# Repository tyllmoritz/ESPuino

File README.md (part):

# ESPuino - rfid-based musiccontroller based on ESP32 with I2S-DAC-support

## NEWS
* As the creator of TonUINO claims it's trademark right, my project has been renamed to ESPuino. I'm totally respecting this and have to admit that I've been not aware of that. However, I instantly renamed everything and hopefully I didn't forget any parts. Since my repository has moved, please make sure (at least if you're using git) to change the URL of your local repository. An explanation was kindly [written by user](https://github.com/biologist79/ESPuino/issues/81).
* Please note: inline with the renaming of the project, MQTT-topics were changed as well as they've been including the old name. Please make sure to change your local MQTT-configuration as well. Sorry to [those](https://github.com/biologist79/ESPuino/issues/83) that spent time on this to point out.
* EN: I've set up a primarily German-speaking community with much documentation. Also an international corner for non-German-speakers is available at https://forum.espuino.de. Github-Login can be used there but it's not necessary.
* DE: Ich habe ein primär deutschsprachiges Forum aufgesetzt, welches ich mit reichlich Doku versehen habe. Würde mich freuen, euch dort zu sehen: https://forum.espuino.de. Ihr könnt euch dort mit eurem Github-Login einloggen, jedoch auch "normal" anmelden. Dokumenation findet ihr insbesondere hier: https://forum.espuino.de/c/dokumentation/anleitungen/10
## Changelog
Moved to [another location](changelog.md) as it became to prominent here. Only last three events are kept:
* 25.02.2020: Added support for dynamic button-layout. Rotary-encoder is now optional and up to five buttons can be used.
* 25.02.2020: Actions can be freely assigned to buttons (multi-button(s), single-button(s) (short), single-button(s) (long))
* 25.02.2020: Added support for webcontrol: basic control (volume, play/pause, next, previous, first, last track) can now be controlled via webgui.
* 25.02.2020: Added support for .m4a and .wav-files.
* 26.02.2020: Shutdown via webgui is now available.
Thanks @QDaniel for the idea + basic implementation (first three features named above)!
## Known bugs
* Some webstreams don't run. Guess it's a combination of saturated connection-pool and lack of heap-memory. Works probably better if ESP32-WROVER (e.g. Lolin D32 pro) is used, as this chip has PSRAM. Advice: Don't enable modules (e.g. MQTT) if you don't need them as this could save memory (and trouble).
* English translation for webgui is currently pretty outdated. This will be fixed soon when i18n-support will be integrated.
## ESPuino - what's that?
The basic idea of ESPuino is to provide a way, to use the Arduino-platform for a music-control-concept that supports locally stored music-files without DRM-restrictions. This basically means that RFID-tags are used to direct a music-player. Even for kids this concept is simple: place an RFID-object (card, character) on top of a box and the music starts to play. Place another RFID-object on it and anything else is played. Simple as that.

The core of my implementation is based on the popular [ESP32 by Espressif](https://www.espressif.com/en/products/hardware/esp32/overview). Having WiFi-support out-of-the-box makes it possible to provide further features like an integrated FTP-server (to feed the player with music), smarthome-integration via MQTT, webradio and administration via webgui. However, my primary focus was to port the project to a modular base. Said this mp3-decoding is done in software with a dedicated uSD-card-slot and music-output is done via I2S-protocol. I did all my tests on [Adafruit's MAX98357A](https://learn.adafruit.com/adafruit-max98357-i2s-class-d-mono-amp/pinouts), [UDA1334](https://www.adafruit.com/product/3678) and [headphone-pcb](https://github.com/biologist79/ESPuino/tree/master/PCBs/Headphone%20with%20PCM5102a%20and%20TDA1308). Hopefully, not only in theory, other DACs that support I2S can be used as well.

## Hardware-setup
The heart of my project is an ESP32 on a [Wemos Lolin32 development-board](https://www.ebay.de/itm/4MB-Flash-WEMOS-Lolin32-V1-0-0-WIFI-Bluetooth-Card-Based-ESP-32-ESP-WROOM-32/162716855489). If ordered in China (Aliexpress, eBay e.g.) it's pretty cheap (around 4€) but even in Europe it's only around 8€. Make sure to install the drivers for the USB/Serial-chip (CP2102 e.g.). But probably it's better to use it's successor (which has battery-measurement already included): [Wemos Lolin D32](https://de.aliexpress.com/item/32808551116.html). Or, if you're planning to hear webstreams regularly, [Wemos Lolin D32 pro](https://de.aliexpress.com/item/32883116057.html) might be a good decision. It comes with uSD-slot onboard and because of its ESP32-WROVER-B has PSRAM included. PSRAM is used as webstream-cache and might be used more intensively in future.
* [MAX98357A (like Adafruit's)](https://de.aliexpress.com/item/32999952454.html)
* [uSD-card-reader; 3.3V only; supports SPI + SD-MMC](https://www.ebay.de/itm/Micro-SPI-Kartenleser-Card-Reader-2GB-SD-8GB-SDHC-Card-3-3V-ESP8266-Arduino-NEU/333796577968) or [cheaper](https://de.aliexpress.com/item/4000899753727.html)
* [RFID-reader RC-522](https://www.amazon.de/AZDelivery-Reader-Arduino-Raspberry-gratis/dp/B074S8MRQ7)
* [RFID-reader PN5180](https://de.aliexpress.com/item/4001278551831.html)
* [RFID-tags](https://www.amazon.de/AZDelivery-Keycard-56MHz-Schlüsselkarte-Karte/dp/B07TVJPTM7)
* [Neopixel-ring](https://de.aliexpress.com/item/32673883645.html)
* [Rotary Encoder](https://de.aliexpress.com/item/33041814942.html)
* [Buttons](https://de.aliexpress.com/item/32896285438.html)
* [Speaker](https://www.visaton.de/de/produkte/chassiszubehoer/breitband-systeme/fr-7-4-ohm)
* uSD-card: doesn't have to be a super-fast one; µC is limiting the throughput. Tested 32GB without any problems.
* uSD in SD-MMC (1 Bit) mode: Several devkits with onboard SD slot have support for this mode, e.g.: (https://de.aliexpress.com/item/4001229463219.html)
* optional replace the RFID-reader with a the better one: PN5180 comes with better RFID-range, less power-consumption and support for ISO-15693 / iCode SLIX2 tags (https://www.bing.com/shop?q=pn5180&FORM=SHOPTB)

## Getting Started
* Arduino-IDE can be used but you need to satisfy dependencies for all the libraries listed in `platformio.ini` manually.
* Instead I recommend to install Microsoft's [Visual Studio Code](https://code.visualstudio.com/). This is a popular and powerful IDE that gives you the ability to install tons of (well-supported) plugins.
* Install [Platformio Plugin](https://platformio.org/install/ide?install=vscode) into [Visual Studio Code](https://code.visualstudio.com/) and make sure to have a look at the [documentation](https://docs.platformio.org/en/latest/integration/ide/pioide.html). Step-by-step-manual is available [here](https://randomnerdtutorials.com/vs-code-platformio-ide-esp32-esp8266-arduino/.)
* Install [Git](https://git-scm.com/downloads) and make a copy ("clone") my repository to your local computer using `git clone https://github.com/biologist79/ESPuino.git`. Using git you can keep your local repository easily up to date without doing copy'n'paste. To keep it up to date run `git pull origin master`. Further infos [here}(https://stackoverflow.com/questions/1443210/updating-a-local-repository-with-changes-from-a-github-repository).
* (Optional) Install [Gitlens](https://marketplace.visualstudio.com/items?itemName=eamodio.gitlens) as plugin (to have advanced Git-support).
* Now, that the git-repository is saved locally, import this folder into Platformio as a project.
* There's a file called `platformio.ini`, that contains the configuration for different develboards (e.g. env:lolin32). Platformio supports hundrets of boards out of the box. So probably you need to change/extend that configuration. Guess Lolin32 is described in platformio.ini but you need Lolin D32, then lookup Platformio's [documentation](https://docs.platformio.org/en/latest/boards/espressif32/lolin_d32.html) to know what to change.
* `upload_port` and `monitor_port` should be autodetected (by the USB-ID of the serial-adapter). If this fails, please set these values depending on your operating system (Windows, Mac OS, Linux).
* Edit `src/settings.h` according your needs. Especially don't forget to set `HAL` depending on your develboard.
* Edit board-specific (`HAL`) config-file (e.g. `settings-lolin32.h` for Lolin32 or `settings-lolin_d32.h` for Lolin D32). If you're running a board that is not listed there: start with `settings-custom.h` and change it according your needs.
* Connect your develboard via USB, click the alien-head to the left and run `Upload and Monitor`. All libraries necessary should be fetched in background now followed by code-compilation. After that, your ESP32 is flashed with the firmware. Depending on your develboard it might me necessary to push a button in order to allow ESP32 to enter flashmode (not necessary für Lolin32, D32 und D32 pro).
* Now have a look at the serial-output at the bottom of Visual Studio Code's windows. At the first run there might appear a few error-messages (related to missing entries in NVS). Don't worry, this is just normal. However, make sure SD is running as this is mandatory!
* If everything ran fine, at the first run, ESPuino should open an access-point with the name "ESPuino". Join this WiFi with your computer (or mobile) and enter `192.168.4.1` to your webbrowser. Enter WiFi-credentials and the hostname. After saving the configuraton, restart ESPuino. Hint: I tried to connect this access-point via Android mobile. Basically that's no problem, but as my mobile detected there'd be no internet-connection, it keept LTE-connection open and prevented me from connecting to `192.168.4.1`. So if in doubts use a computer.
* After reboot ESPuino tries to join your WiFi (with the credentials previously entered). If that was successful, an IP is shown in the serial-console of Visual Studio Code. You can call ESPuino's GUI using a webbrowser via this IP; make sure to allow Javascript. If mDNS-feature is active in `src/settings.h`, you can use the hostname configured extended by .local instead the IP. So if you configured `espuino` as hostname, you can use `espuino.local` for webgui and FTP.
* Via FTP you can upload data (but don't expect it to be super fast). It's round about 185 kb/s if SD is in SPI-mode and 310 kB/s if SD is in MMC-mode.
* FTP needs to be activated after boot! Don't forget to assign action `ENABLE_FTP_SERVER` in `settings.h` to be able to activate it. Neopixel flashes green (1x) if enabling was successful. It'll be disabled automatically after next reboot. Means: you have to enable it every time you need it (if reboot was in between). Sounds annoying and maybe it is, but's running this way in order to have more heap-memory available (for webstream) if FTP isn't running.
* Via webbrowser you can configure various settings and pair RFID-tags with actions. If MQTT/FTP-support was not compiled, their config-tabs won't appear.

## Prerequisites / tipps
* Open settings.h
* choose if optional modules (e.g. MQTT, FTP, Neopixel) should be compiled/enabled
* Make sure to edit/review button-layout. Default-design is three buttons and a rotary-encoder. All actions available are listed in `values.h` (values >= 100).
* For debugging-purposes serialDebug can be set to ERROR, NOTICE, INFO or DEBUG.
* If MQTT=yes, set the IP or hostname of the MQTT-server accordingly and check the MQTT-topics (states and commands)
* Advice: don't enable MQTT if there's no broker around because network-timeouts can really be a PITA.
* If Neopixel enabled: set NUM_LEDS to the LED-number of your Neopixel-ring and define the Neopixel-type using `#define CHIPSET`
* If you're using Arduino-IDE please make sure to change ESP32's partition-layout to `No OTA (2MB APP/2MB Spiffs)` as otherwise the sketch won't fit into the flash-memory.
* Open board-specific config-file and edit according your needs.
* If you want to monitor battery's voltage, make sure to enable `MEASURE_BATTERY_VOLTAGE`. Use a voltage-divider as voltage of a LiPo is way too high for ESP32 (only 3.3V supported!). For my tests I connected VBat with a serial connection of 130k + 130k resistors (VBat(+)--130k--X--130k--VBat(-)). X is the measure-point where to connect the GPIO to. If using Lolin D32 or Lolin D32 pro, make sure to leave both resistor-values unchanged at 100k. Same for GPIO: unchanged at 35.
Please note: via GUI upper and lower voltage cut-offs for visualisation of battery-voltage (Neopixel) is available. Additional GUI-configurable values are interval (in minutes) for checking battery voltage and the cut off-voltage below whose a warning is shown via Neopixel.
* If you're using a headphone-pcb with a [headphone jack](https://www.conrad.de/de/p/cliff-fcr1295-klinken-steckverbinder-3-5-mm-buchse-einbau-horizontal-polzahl-3-stereo-schwarz-1-st-705830.html) that has a pin to indicate if there's a plug, you can use this signal along with the feature `HEADPHONE_ADJUST_ENABLE` to limit the maximum headphone-voltage automatically. As per default you have to invert this signal (with a P-channel MOSFET) and connect it to GPIO22.
* Enabling `SHUTDOWN_IF_SD_BOOT_FAILS` is really recommended if you run your ESPuino in battery-mode without having a restart-button exposed to the outside of ESPuino's enclosure. Because otherwise there's no way to restart your ESPuino and the error-state will remain until battery is empty (or you open the enclosure, hehe).
* Enabling `PLAY_LAST_RFID_AFTER_REBOOT` will tell ESPuino to remember the last RFID-tag played after next reboot. So rebooting ESPuino will end up in autoplay. I don't really recommend this feature because if you use it along with a webstream, in case of streaming-issues this might end up in an infinite loop.

## SD-card: SPI or SD-MMC (1 bit)-mode?
Having SD working is mandatory. However, there are two modes available to access SD-cards: SPI and SD-MMC (1 bit).<br />
Advantages SD-MMC (1 bit) over SPI:
* Needs only three GPIOs (instead of four)
* It's faster. FTP-upload: 298 kiB vs 178 kiB. HTTP-upload: 372 kiB vs 184 kiB. (tested with filesize of 70.7 MiB.<br />
So why using SPI if SD-MMC seems to be better? The primary problem of SD-MMC is: you cannot choose different GPIOs. That doesn't sound bad but this can (depending on the uSD-card-reader-module) be a problem because maybe GPIO2 is pulled HIGH to 3.3V by a 10k-resistor. For example this is the case when using the reader-module named above in hardware-setup. It's a problem because if GPIO2 is pulled high at boot, ESP32 doesn't enter flash-mode. As soon as flash-mode is entered, it's no longer a problem. However, this behaviour can be an issue if ESP32 is deeply "burried" in ESPuino's enclosure and you want to update its firmware. But fortunately there's a way to bypass this problem: remove the [pullup-resistor shown in the picture](https://raw.githubusercontent.com/biologist79/ESPuino/master/pictures/Pullup-removal.jpg). It can be removed safely because if MMC-mode is set, pullup is done in software using `pinMode(2, INPUT_PULLUP);`. So it's not really a problem but you have to take note of that!

## RFID: RC522 or PN5180?
RC522 is so to say the Tonuino-standard. It's cheap and works, but RFID-tag has to be placed near the reader. PN5180 instead has better RFID range/sensitivity and can read ISO-15693 / iCode SLIX2-tags aka 'Tonies' (you need a password to read Tonies). You can also wake-up the board with the card. Disadvantages: is a bit more expensive and needs more GPIOs (6/7 instead of 4). Refer PN5180's wire-section below for further informations. Hint: if using 3.3V make sure to connect PN5180 to +5V AND 3.3V. Sounds weird but it's necessary.

## 3.3 or 5V?
* Why 3.3V? Because: if you plan to use battery-mode with a LiPo, there's no 5 V available (unless USB is connected).
That's why my design's focus is 3.3 V. If you want to use 5 V - do so, but be advised it's not compatible with LiPo-battery-mode. The Mosfet-circuit for saving power in deepsleep (see [Lolin32-schematics](https://github.com/biologist79/ESPuino/blob/master/PCBs/Wemos%20Lolin32/Pictures/Tonuino%20V2-Schematics.pdf) as reference) works as well for 5 V.
* MAX98357a: provides more power at 5 V but also runs at 3.3 V. Anyway: it's still loud enough (in my opinion).
* Neopixel: specification says it needs 5 V but also runs at 3.3 V.
* RC522: needs 3.3 V (don't power with 5 V!)
* PN5180: at 3.3 V make sure to connect both 5 V and 3.3 V-pins to 3.3 V.
* SD: needs 3.3 V but if voltage-regulator is onboard, it can be connected to 5 V as well
* Rotary encoder: 3.3 V (don't power with 5 V! Encoder doens't care if connected to 3.3 or 5 V, but GPIOs of ESP32 do!)

## Wiring (general)
Depending on the develboard you're using and the needs you have, there are different options available.
A lot of wiring is necessary to get ESPuino working. After my first experiments on a breadboard I soldered all the stuff onto a PCB in order to avoid wild-west-cabling. Especially for the interconnect between µC and uSD-card-reader make sure to use short wires (like 10cm or so)! As of my experience with a breadbord, male/male-connectors are better than female/female-connectors. Important: you can easily connect another I2S-DACs by just connecting them in parallel to the I2S-pins (DIN, BCLK, LRC). This is true for example if you plan to integrate a [line/headphone-pcb](https://www.adafruit.com/product/3678). In general, this runs fine. But unfortunately especially this board lacks of a headphone jack, that takes note if a plug is inserted or not. Best way is to use a [headphone jack](https://www.conrad.de/de/p/cliff-fcr1295-klinken-steckverbinder-3-5-mm-buchse-einbau-horizontal-polzahl-3-stereo-schwarz-1-st-705830.html) that has a pin that is pulled to GND, if there's no plug and vice versa. Using for example a MOSFET-circuit, this GND-signal can be inverted in a way, that MAX98357.SD is pulled down to GND if there's a plug. Doing that will mute MAX98537a and so turn off the speaker immediately if there's a plug and vice versa. Have a look at the PCB-folder in order to view the detailed solution. Here's an example for such a [headphone-pcb](https://github.com/biologist79/ESPuino/tree/master/PCBs/Headphone%20with%20PCM5102a%20and%20TDA1308) that makes use of GND.<br />
Have a look at the PCB-folder. I provided PCBs for a number of develboards. Probably this makes things easier for you.

## Wiring (2 SPI-instances: RC522 + SD + 3 buttons + rotary-encoder)
Uses two SPI-instances. The first one for the RFID-reader and the second for SD-card-reader. This is also the [setup, I personally use](https://github.com/biologist79/ESPuino/tree/master/PCBs/Wemos%20Lolin32).<br />
| ESP32 (GPIO)  | Hardware              | Pin    | Comment                                                      |
| ------------- | --------------------- | ------ | ------------------------------------------------------------ |
| 3.3 (5) V     | SD-reader             | VCC    | Connect to p-channel MOSFET for power-saving when µC is off  |
| GND           | SD-reader             | GND    |                                                              |
| 15            | SD-reader             | CS     |                                                              |
| 13            | SD-reader             | MOSI   |                                                              |
| 16            | SD-reader             | MISO   |                                                              |
| 14            | SD-reader             | SCK    |                                                              |
| 3.3 V         | RFID-reader           | 3.3V   | (Connect directly to GPIO 17 for power-saving when µC is off)  |
| GND           | RFID-reader           | GND    |                                                              |
| 21            | RFID-reader           | CS/SDA |                                                              |
| 23            | RFID-reader           | MOSI   |                                                              |
| 19            | RFID-reader           | MISO   |                                                              |
| 18            | RFID-reader           | SCK    |                                                              |
| 5 / 3.3 V     | MAX98357              | VIN    | Connect to p-channel MOSFET for power-saving when µC is off  |
| GND           | MAX98357              | GND    |                                                              |
| 25            | MAX98357              | DIN    |                                                              |
| 27            | MAX98357              | BCLK   |                                                              |
| 26            | MAX98357              | LRC    |                                                              |
| ---           | MAX98357              | SD     | Info: if pulled down to GND amp will turn off                |
| 34            | Rotary encoder        | CLK    | Change CLK with DT if you want to change the direction of RE |
| 35            | Rotary encoder        | DT     | Change CLK with DT if you want to change the direction of RE |
| 32            | Rotary encoder        | BUTTON |                                                              |
| 3.3 V         | Rotary encoder        | +      |                                                              |
| GND           | Rotary encoder        | GND    |                                                              |
| 4             | Button (next)         |        |                                                              |
| GND           | Button (next)         |        |                                                              |
| 2             | Button (previous)     |        |                                                              |
| GND           | Button (previous)     |        |                                                              |
| 5             | Button (pause/play)   |        |                                                              |
| GND           | Button (pause/play)   |        |                                                              |
| 3.3 V         | Neopixel              | V      | Connect to p-channel MOSFET for power-saving when µC is off  |
| GND           | Neopixel              | G      |                                                              |
| 12            | Neopixel              | DI     |                                                              |
| 17            | N-channel Mosfet      | Gate   |                                                              |
| 33            | Voltage-divider / BAT |        | Optional: voltage-divider to monitor battery-voltage         |
| 22            | Headphone jack        |        | Optional: if pulled to ground, headphone-volume is set       |

Optionally, GPIO 17 can be used to drive a Mosfet-circuit in order to switch off peripherals (SD, Neopixel, RFID and MAX98357a) if ESP32 is in deepsleep. Please refer the schematics for my [Lolin32-PCB](https://github.com/biologist79/ESPuino/blob/master/PCBs/Wemos%20Lolin32/Pictures/Tonuino-Lolin32-Schematics.pdf) for further informations. If you need further informations on transistor-circuits visit this [website](https://dl6gl.de/schalten-mit-transistoren.html). <br />
In general I recommend using a [uSD-card-reader](https://www.ebay.de/itm/Micro-SPI-Kartenleser-Card-Reader-2GB-SD-8GB-SDHC-Card-3-3V-ESP8266-Arduino-NEU/333796577968) that can be run solely with 3.3V (doesn't have a voltage-regulator). This is because if 3.3V go through the voltage regulator a small voltage-drop will be introduced, which may lead to SD-malfunction as the resulting voltage is a bit too low. Vice versa if you want to connect your reader solely to 5V, make sure to have one WITH a voltage regulator :-). And by the way: when LiPo-battery is connected, there's no 5V. That's why I designed my [Lolin-PCBs](https://github.com/biologist79/ESPuino/tree/master/PCBs/Wemos%20Lolin32) with 3.3V only.

## Wiring (SD-card in 1 Bit SD-MMC mode) different to above
| ESP32 (GPIO)  | Hardware              | Pin    | Comment                                                      |
| ------------- | --------------------- | ------ | ------------------------------------------------------------ |
| --            | SD-reader             | CS     | no CS required                                               |
| 15            | SD-reader             | MOSI   |                                                              |
| 2             | SD-reader             | MISO   | make sure there's no [hardware-pullup](https://raw.githubusercontent.com/biologist79/ESPuino/master/pictures/Pullup-removal.jpg) for MISO |
| 14            | SD-reader             | SCK    |                                                              |

Make sure to enable `SD_MMC_1BIT_MODE` if you want to use this feature. Don't(!) enable `SINGLE_SPI_ENABLE`. SD-MMC-mode requires these fixed PINs listed above. You can find a good comparison of different SD-card-modes here: (https://www.instructables.com/Select-SD-Interface-for-ESP32/).
Advice: Double check that above PINs are not used elsewhere (e.g. GPIO2 is used as PREVIOUS_BUTTON as per default in settings.h).

## Wiring (1 SPI-instance: RC522 + SD + 3 buttons + rotary-encoder) [EXPERIMENTAL, maybe not working!]
Basically the same as using 2 SPI-instances but...
In this case RFID-reader + SD-reader share SPI's SCK, MISO and MOSI. But make sure to use different CS-pins. Have to admit I had some problems to get this running. Seems to be connected properly, but nothing happens when an RFID-tag is applied. Maybe anybody else wants to point out :-)

| ESP32 (GPIO)  | Hardware              | Pin    | Comment                                                      |
| ------------- | --------------------- | ------ | ------------------------------------------------------------ |
| 3.3 (5) V     | SD-reader             | VCC    | Connect to p-channel MOSFET for power-saving when µC is off  |
| GND           | SD-reader             | GND    |                                                              |
| 15            | SD-reader             | CS     | Don't share with RFID!                                       |
| 3.3 V         | RFID-reader           | 3.3V   | Connect directly to GPIO 17 for power-saving when µC is off  |
| GND           | RFID-reader           | GND    |                                                              |
| 21            | RFID-reader           | CS/SDA | Don't share with SD!                                         |
| 23            | RFID+SD-reader        | MOSI   |                                                              |
| 19            | RFID+SD-reader        | MISO   |                                                              |
| 18            | RFID+SD-reader        | SCK    |                                                              |
| 5 / 3.3 V     | MAX98357              | VIN    | Connect to p-channel MOSFET for power-saving when µC is off  |
| GND           | MAX98357              | GND    |                                                              |
| 25            | MAX98357              | DIN    |                                                              |
| 27            | MAX98357              | BCLK   |                                                              |
| 26            | MAX98357              | LRC    |                                                              |
| ---           | MAX98357              | SD     | Info: if pulled down to GND amp will turn off                |
| 34            | Rotary encoder        | CLK    | Change CLK with DT if you want to change the direction of RE |
| 35            | Rotary encoder        | DT     | Change CLK with DT if you want to change the direction of RE |
| 32            | Rotary encoder        | BUTTON |                                                              |
| 3.3 V         | Rotary encoder        | +      |                                                              |
| GND           | Rotary encoder        | GND    |                                                              |
| 4             | Button (next)         |        |                                                              |
| GND           | Button (next)         |        |                                                              |
| 2             | Button (previous)     |        |                                                              |
| GND           | Button (previous)     |        |                                                              |
| 5             | Button (pause/play)   |        |                                                              |
| GND           | Button (pause/play)   |        |                                                              |
| 5 / 3.3 V     | Neopixel              | V      | Connect to p-channel MOSFET for power-saving when µC is off  |
| GND           | Neopixel              | G      |                                                              |
| 12            | Neopixel              | DI     |                                                              |
| 17            | N-channel Mosfet      | Gate   |                                                              |
| 33            | Voltage-divider / BAT |        | Optional: voltage-divider to monitor battery-voltage         |
| 22            | Headphone jack        |        | Optional: if pulled to ground, headphone-volume is set       |

## Wiring (PN5180 instead of MFRC522) different to above
PN5180-reader needs at least two more GPIOs: RESET and BUSY. Double check pin-conflicts! `RFID_READER_TYPE_PN5180` needs to be enabled to use this feature. Make sure to disable `RFID_READER_TYPE_MFRC522` if doing so!
You can enable low power card-detection with `PN5180_ENABLE_LPCD`, but this needs another GPIO for IRQ. With low power card detection (LPCD) you can wake-up the ESP32 from deep-sleep just by applying a card to the reader. You need a PN5180-firmware >= 4.0. Most china-boards comes with older firmware. The latest firmware can be flashed with this [project](https://github.com/abidxraihan/PN5180_Updater_ESP32).

| ESP32 (GPIO)  | Hardware              | Pin    | Comment                                                           |
| ------------- | --------------------- | ------ | ----------------------------------------------------------------- |
| 3.3 V         | PN5180 RFID-reader    | 3.3V   | Connect directly to GPIO 17 for power-saving when µC is off       |
| 3.3 V         |                       | 3.3V   | For low power card detection mode (LPCD) connect directly to 3.3V |
| 5 / 3.3 V     | PN5180 RFID-reader    | 5V     | Don't forget to connect this pin the same way as 3.3V             |
| GND           | PN5180 RFID-reader    | GND    |                                                                   |
| 21            | PN5180 RFID-reader    | CS/SDA | Same as MFRC522. Don't share with SD!                             |
| 23            | PN5180 RFID-reader    | MOSI   | Same as MFRC522                                                   |
| 19            | PN5180 RFID-reader    | MISO   | Same as MFRC522                                                   |
| 18            | PN5180 RFID-reader    | SCK    | Same as MFRC522                                                   |
| 16            | PN5180 RFID-reader    | BUSY   | be aware of SD MISO if running in SPI mode                        |
| 22            | PN5180 RFID-reader    | RST    | be aware of Headphone jack PIN                                    |
| 39            | PN5180 RFID-reader    | IRQ    | optional, used for low power card detection (LPCD)                |

## Wiring (custom) / different pinout
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
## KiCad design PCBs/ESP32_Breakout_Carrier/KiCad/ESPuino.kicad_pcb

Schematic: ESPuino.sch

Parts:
J1: SD-Card Reader; PinHeader_1x06_P2.54mm_Vertical
J2: RFID-RC522; PinHeader_1x08_P2.54mm_Vertical
J3: Adafruit MAX98357; PinHeader_1x07_P2.54mm_Vertical
J4: Rotary Encode; PinHeader_1x05_P2.54mm_Vertical
J5: Next; PinHeader_1x02_P2.54mm_Vertical
J6: Prev; PinHeader_1x02_P2.54mm_Vertical
J7: Pause; PinHeader_1x02_P2.54mm_Vertical
J8: WS2812; PinHeader_1x03_P2.54mm_Vertical
J9: Power; PinHeader_1x02_P2.54mm_Vertical
Q1: BC337; TO-92_Inline_Wide
Q2: IRF9540N; TO-220-3_Vertical
R1, R4: 10k; 0207_9
R5: 4,7k; 0207_9
U1: ESP32-DEVKITC-32U; MODULE_ESP32-DEVKITC-32U

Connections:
3.3V: J4.2, U1.1
BUTTON_NEXT_PIN: J6.2, U1.26
BUTTON_PLAY_PAUSE_PIN: J7.2, U1.29
BUTTON_PREVIOUS_PIN: J5.2, U1.8
GND: J1.1, J2.3, J3.2, J4.1, J5.1, J6.1, J7.1, J8.1, J9.1, Q1.3 (E), R4.2, U1.14, U1.32, U1.38
GPIO-17: J2.1, R5.2, U1.28
MAX98357_BLCK: J3.6, U1.11
MAX98357_DIN: J3.5, U1.9
MAX98357_LRC: J3.7, U1.10
NEOPIXEL_DI: J8.2, U1.13
unnamed: Q1.1 (C), Q2.1 (G), R1.2
unnamed: Q1.2 (B), R4.1, R5.1
RFID_MISO: J2.5, U1.31
RFID_MOSI: J2.6, U1.37
RFID_RST: J2.2, U1.36
RFID_SCK: J2.7, U1.30
RFID_SDA: J2.8, U1.33
ROTARY_BUTTON: J4.5, U1.7
ROTARY_CLR: J4.3, U1.5
ROTARY_DT: J4.4, U1.6
SD-CARD_CS: J1.6, U1.23
SD-CARD_MISO: J1.3, U1.27
SD-CARD_MOSI: J1.4, U1.15
SD-CARD_SCK: J1.5, U1.12
SWITCHED_VCC: J1.2, J3.1, J8.3, Q2.2 (D)
VCC: J9.2, Q2.3 (S), R1.1, U1.19

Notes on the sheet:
Breakout Boards
Inputs Interfaces
Switched 5V (Deep Sleep)
ESP-32
Power Supply

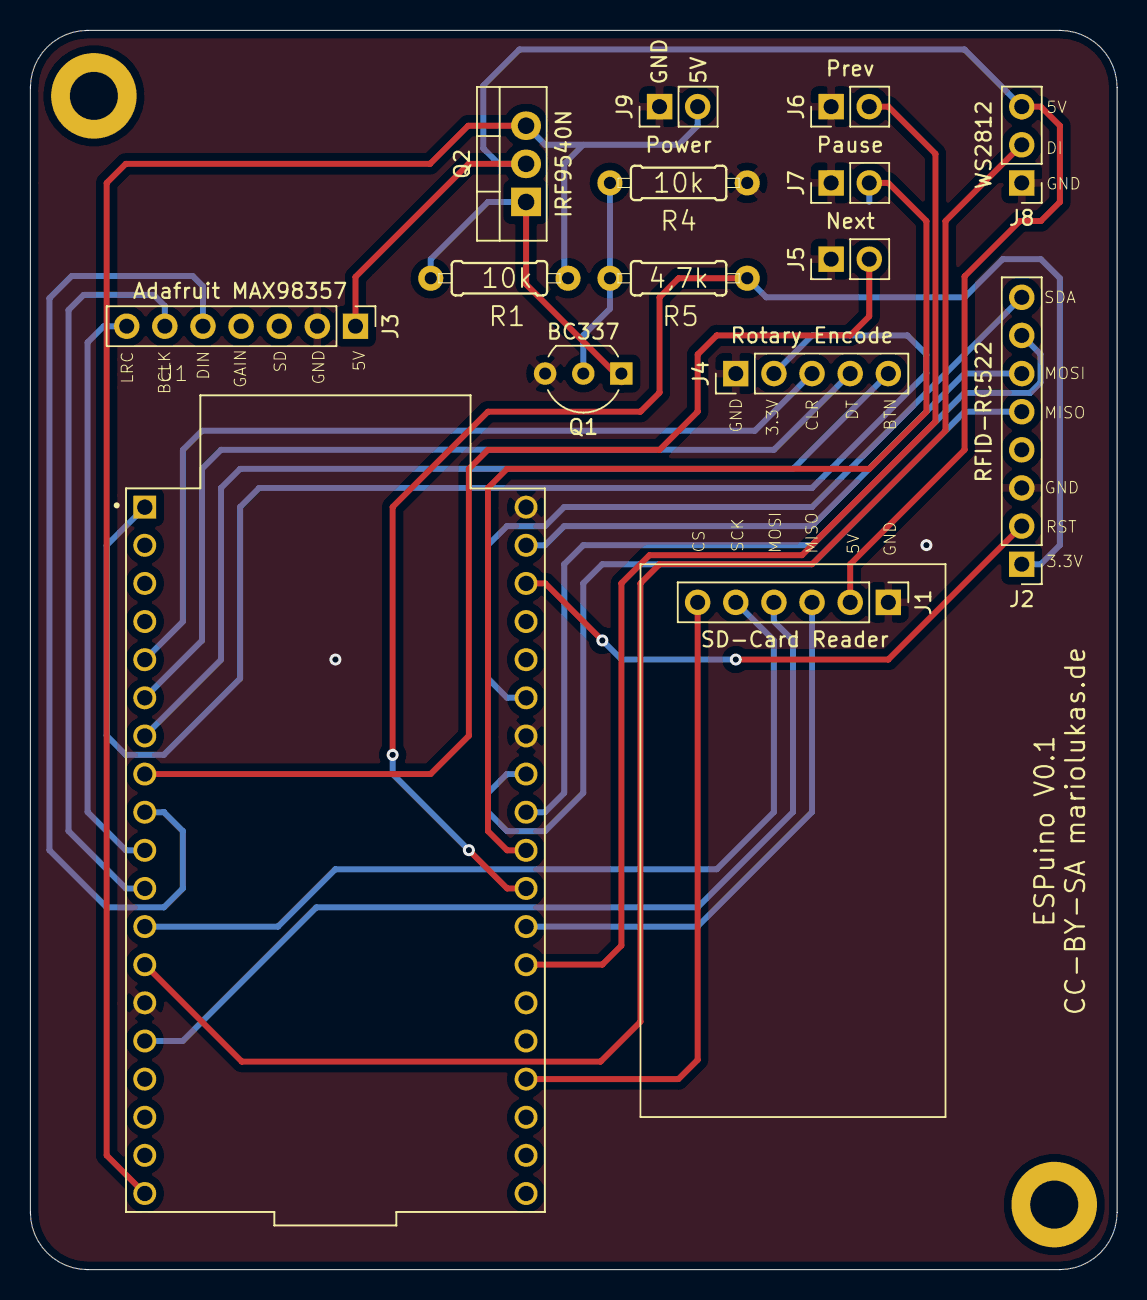
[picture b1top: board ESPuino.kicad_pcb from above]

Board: 2 copper layers, 72.4 x 82.6 mm, 15 parts (0 on the bottom side), 26 nets.

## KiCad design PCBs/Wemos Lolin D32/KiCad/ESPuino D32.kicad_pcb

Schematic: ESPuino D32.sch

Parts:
H1, H2, H3, H4: MountingHole; MountingHole_3.2mm_M3
J1: MAX98357a; PinSocket_1x07_P2.54mm_Vertical
J2: Neopixel; JST_PH_B3B-PH-K_1x03_P2.00mm_Vertical
J3: to_Headphone; IDC-Header_2x03_P2.54mm_Vertical
J4: RotEncoder; JST_PH_B5B-PH-K_1x05_P2.00mm_Vertical
J5: Next-Bt; JST_PH_B2B-PH-K_1x02_P2.00mm_Vertical
J6: RFID; JST_PH_B6B-PH-K_1x06_P2.00mm_Vertical
J7: Prev-Bt; JST_PH_B2B-PH-K_1x02_P2.00mm_Vertical
J8: PPlay-Bt; JST_PH_B2B-PH-K_1x02_P2.00mm_Vertical
J9: Reset; JST_PH_B2B-PH-K_1x02_P2.00mm_Vertical
J10: uSD-Reader; PinSocket_1x06_P2.54mm_Vertical
M1: LolinD32
Q1: NDP6020P; TO-220-3_Vertical
Q2: IRF530NPbF; TO-220-3_Vertical
R1, R3: 100k; R_Axial_DIN0204_L3.6mm_D1.6mm_P7.62mm_Horizontal
R2: 1k; R_Axial_DIN0204_L3.6mm_D1.6mm_P7.62mm_Horizontal
R4: 10k; R_Axial_DIN0204_L3.6mm_D1.6mm_P7.62mm_Horizontal

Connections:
+3V3: J4.2, M1.16 (3V), Q1.3, R3.2
BUT_NEXT: J5.1, M1.21 (4)
BUT_PPLAY: J8.1, M1.24 (5)
BUT_PREV: J7.1, M1.19 (2)
CS_RFID: J6.1, M1.27 (21)
CS_SD: J10.5, M1.18 (15)
DIN: J1.5, J3.1, M1.9 (25)
EN: J9.1, M1.3 (EN)
GND: J1.2, J2.1, J3.4, J4.1, J5.2, J6.5, J7.2, J8.2, J9.2, J10.1, M1.17 (GND), M1.32 (GND), Q2.3, R4.1
Headphone: J1.3, J3.6, M1.30 (22)
I2S_BCLK: J1.6, J3.3, M1.7 (27)
I2S_LRC: J1.7, J3.5, M1.8 (26)
MISO_RFID: J6.4, M1.26 (19)
MISO_SD: J10.2, M1.22 (16)
MOSI_RFID: J6.3, M1.31 (23)
MOSI_SD: J10.4, M1.4 (13)
NEO_DO: J2.2, M1.5 (12)
unnamed: J1.4, R1.1
unnamed: M1.23 (17), R2.2
unnamed: Q1.1, Q2.2, R3.1
unnamed: Q2.1, R2.1, R4.2
ROTENC_BUT: J4.3, M1.11 (32)
ROTENC_CLK: J4.4, M1.12 (34)
ROTENC_DT: J4.5, M1.10 (33)
SCK_RFID: J6.2, M1.25 (18)
SCK_SD: J10.3, M1.6 (14)
SW_Power3.3: J1.1, J2.3, J3.2, J6.6, J10.6, Q1.2, R1.2

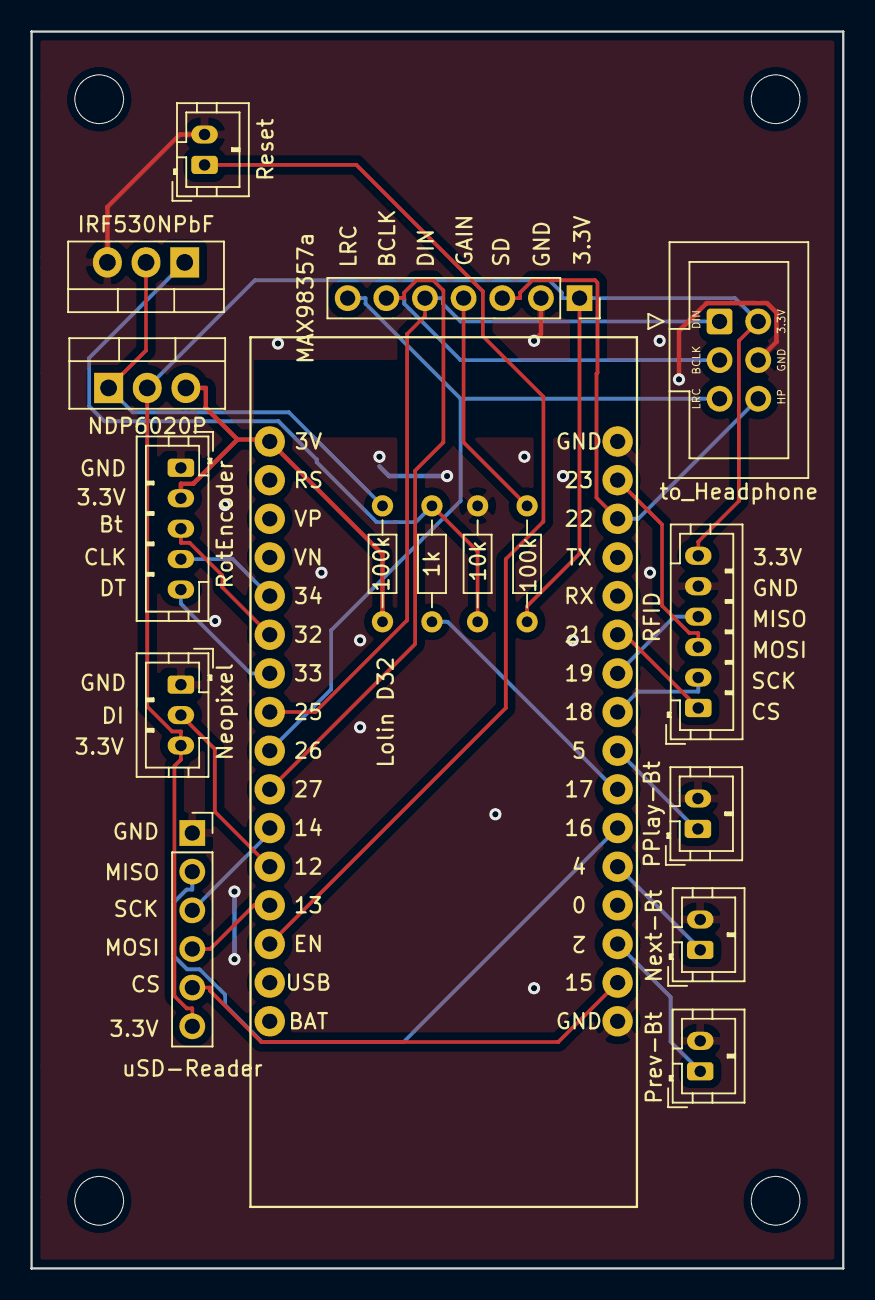
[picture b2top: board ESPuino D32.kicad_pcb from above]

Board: 2 copper layers, 53.3 x 81.3 mm, 21 parts (0 on the bottom side), 27 nets.

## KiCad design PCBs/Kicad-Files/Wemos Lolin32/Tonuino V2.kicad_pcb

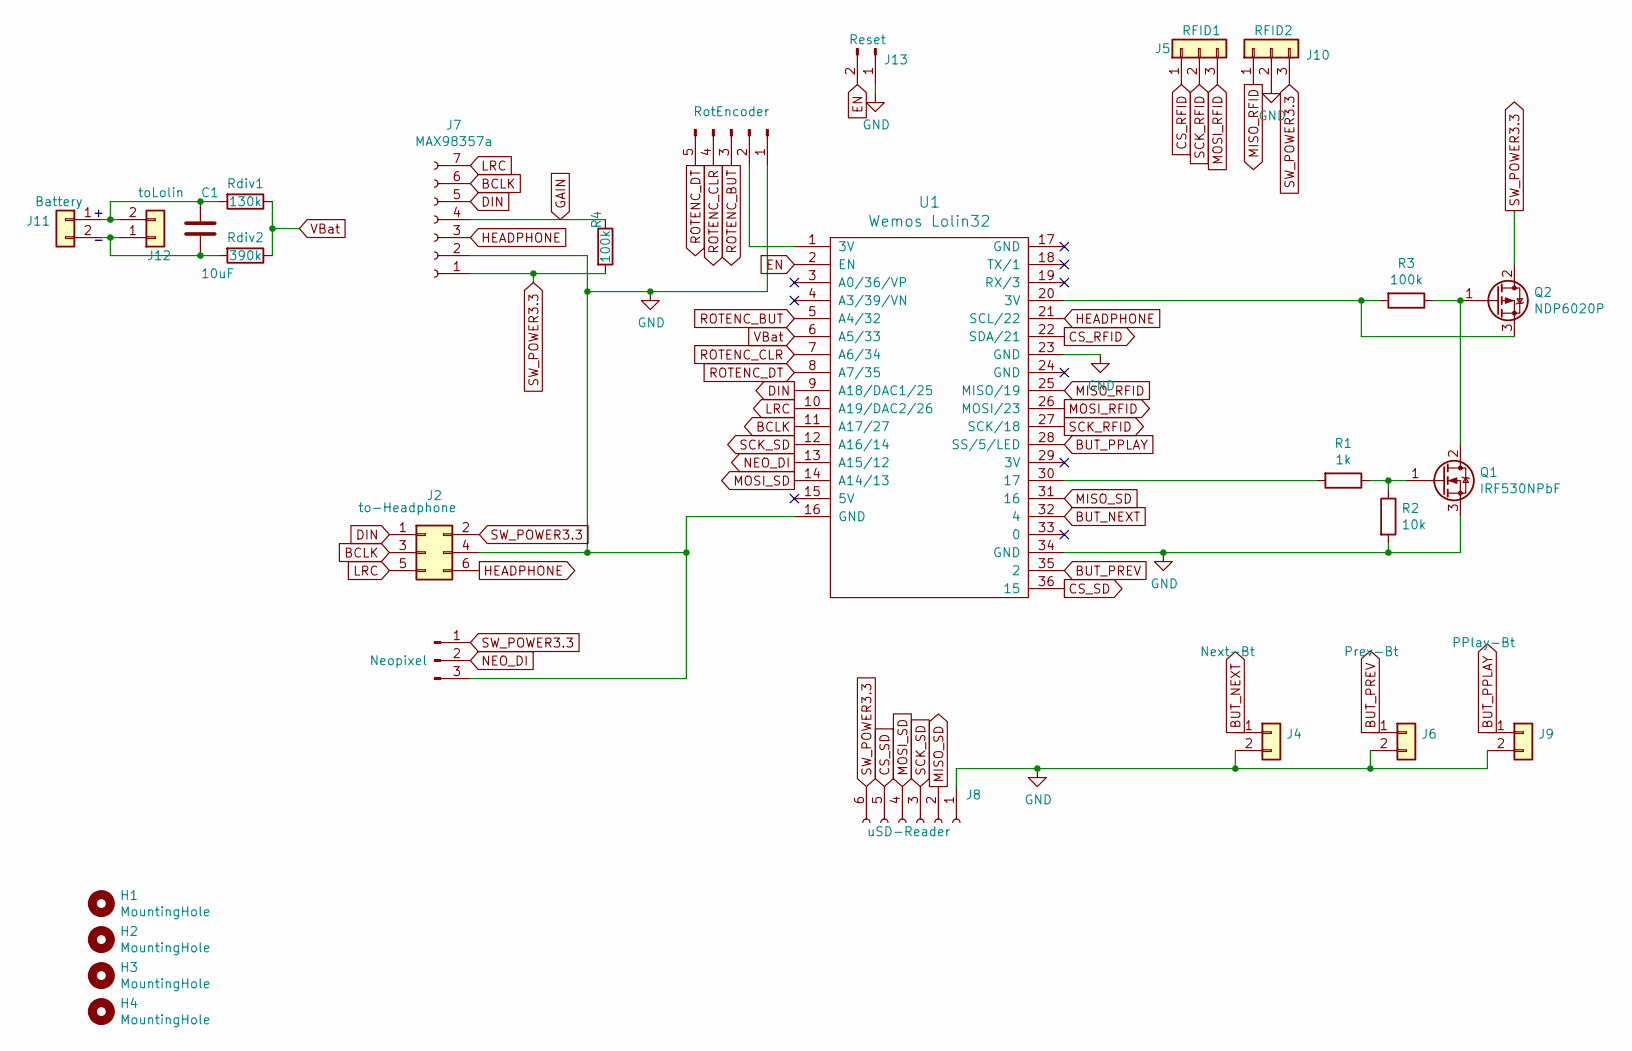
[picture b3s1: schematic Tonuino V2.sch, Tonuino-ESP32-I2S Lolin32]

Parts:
C1: 10uF; CP_Radial_D4.0mm_P2.00mm
H1, H2, H3, H4: MountingHole; MountingHole_3.2mm_M3
J1: Neopixel; JST_PH_B3B-PH-K_1x03_P2.00mm_Vertical
J2: to-Headphone; IDC-Header_2x03_P2.54mm_Vertical
J3: RotEncoder; JST_PH_B5B-PH-K_1x05_P2.00mm_Vertical
J4: Next-Bt; JST_PH_B2B-PH-K_1x02_P2.00mm_Vertical
J5: RFID1; JST_PH_B3B-PH-K_1x03_P2.00mm_Vertical
J6: Prev-Bt; JST_PH_B2B-PH-K_1x02_P2.00mm_Vertical
J7: MAX98357a; PinSocket_1x07_P2.54mm_Vertical
J8: uSD-Reader; PinSocket_1x06_P2.54mm_Vertical
J9: PPlay-Bt; JST_PH_B2B-PH-K_1x02_P2.00mm_Vertical
J10: RFID2; JST_PH_B3B-PH-K_1x03_P2.00mm_Vertical
J11: Battery; JST_PH_B2B-PH-K_1x02_P2.00mm_Vertical
J12: toLolin; PinHeader_1x02_P2.00mm_Vertical
J13: Reset; JST_PH_B2B-PH-K_1x02_P2.00mm_Vertical
Q1: IRF530NPbF; TO-220-3_Vertical
Q2: NDP6020P; TO-220-3_Vertical
R1: 1k; R_Axial_DIN0204_L3.6mm_D1.6mm_P7.62mm_Horizontal
R2: 10k; R_Axial_DIN0204_L3.6mm_D1.6mm_P7.62mm_Horizontal
R3, R4: 100k; R_Axial_DIN0204_L3.6mm_D1.6mm_P7.62mm_Horizontal
Rdiv1: 130k; R_Axial_DIN0204_L3.6mm_D1.6mm_P7.62mm_Horizontal
Rdiv2: 390k; R_Axial_DIN0204_L3.6mm_D1.6mm_P7.62mm_Horizontal
U1: Wemos Lolin32; Lolin32

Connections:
BCLK: J2.3, J7.6, U1.11 (A17/27)
BUT_NEXT: J4.1, U1.32 (4)
BUT_PPLAY: J9.1, U1.28 (SS/5/LED)
BUT_PREV: J6.1, U1.35 (2)
CS_RFID: J5.1, U1.22 (SDA/21)
CS_SD: J8.5, U1.36 (15)
DIN: J2.1, J7.5, U1.9 (A18/DAC1/25)
EN: J13.2, U1.2 (EN)
GAIN: J7.4, R4.1
GND: J1.3, J2.4, J3.1, J4.2, J6.2, J7.2, J8.1, J9.2, J10.2, J13.1, Q1.3 (S), R2.2, U1.16 (GND), U1.23 (GND), U1.34 (GND)
HEADPHONE: J2.6, J7.3, U1.21 (SCL/22)
LRC: J2.5, J7.7, U1.10 (A19/DAC2/26)
MISO_RFID: J10.1, U1.25 (MISO/19)
MISO_SD: J8.2, U1.31 (16)
MOSI_RFID: J5.3, U1.26 (MOSI/23)
MOSI_SD: J8.4, U1.14 (A14/13)
NEO_DI: J1.2, U1.13 (A15/12)
unnamed: C1.1, J11.1, J12.2, Rdiv1.2
unnamed: C1.2, J11.2, J12.1, Rdiv2.2
unnamed: J3.2, U1.1 (3V)
unnamed: Q1.1 (G), R1.1, R2.1
unnamed: Q1.2 (D), Q2.1 (G), R3.1
unnamed: Q2.3 (S), R3.2, U1.20 (3V)
unnamed: R1.2, U1.30 (17)
ROTENC_BUT: J3.3, U1.5 (A4/32)
ROTENC_CLR: J3.4, U1.7 (A6/34)
ROTENC_DT: J3.5, U1.8 (A7/35)
SCK_RFID: J5.2, U1.27 (SCK/18)
SCK_SD: J8.3, U1.12 (A16/14)
SW_POWER3.3: J1.1, J2.2, J7.1, J8.6, J10.3, Q2.2 (D), R4.2
VBat: Rdiv1.1, Rdiv2.1, U1.6 (A5/33)

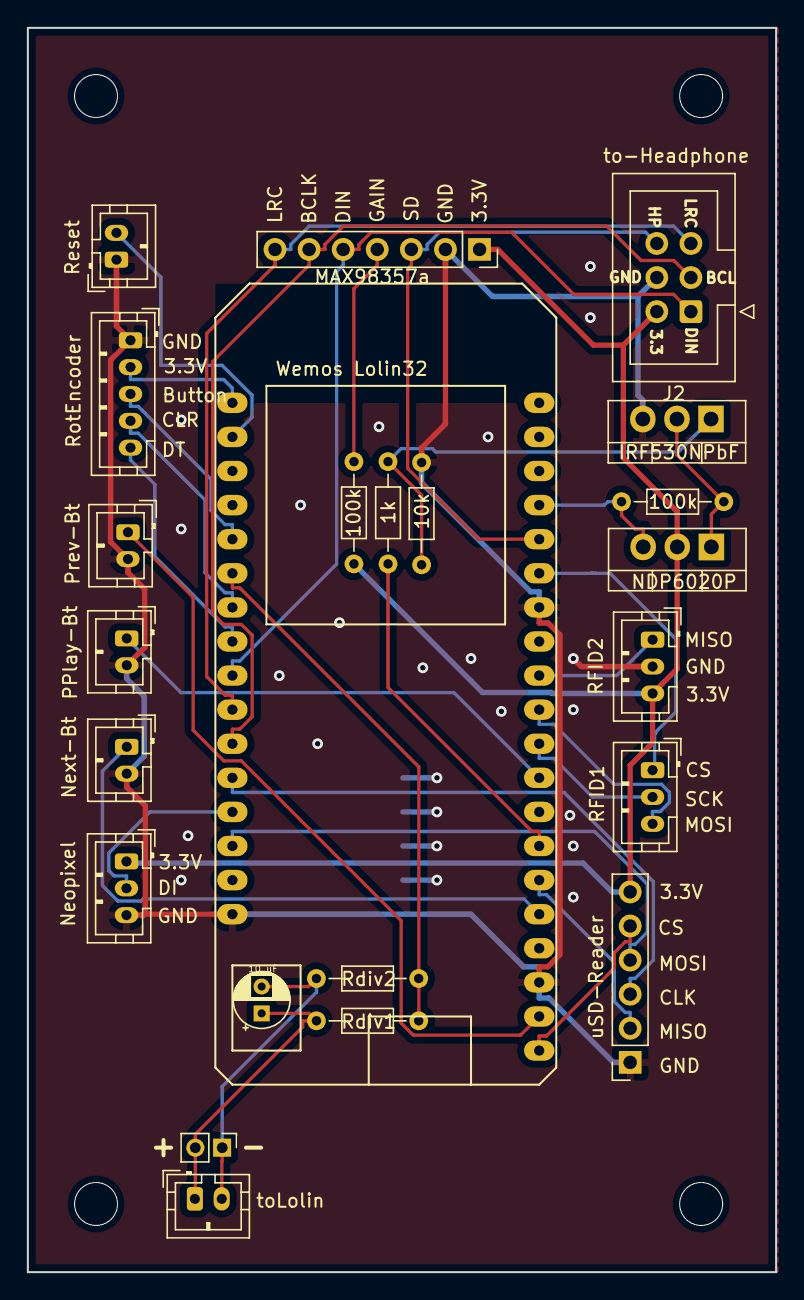
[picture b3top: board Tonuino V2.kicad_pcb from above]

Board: 2 copper layers, 55.8 x 92.7 mm, 27 parts (0 on the bottom side), 31 nets.

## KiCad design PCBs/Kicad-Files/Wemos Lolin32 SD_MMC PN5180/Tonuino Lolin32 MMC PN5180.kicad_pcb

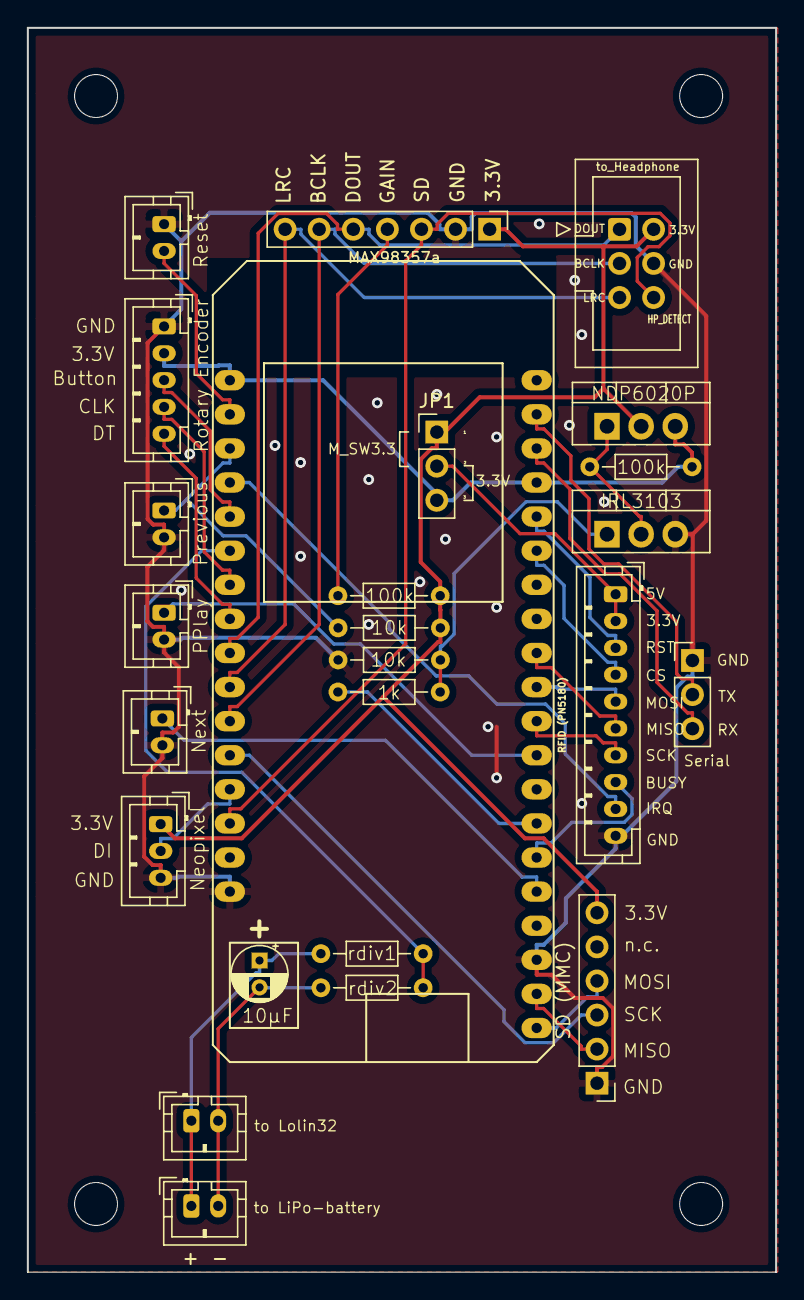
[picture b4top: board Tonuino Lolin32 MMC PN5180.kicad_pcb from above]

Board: 2 copper layers, 55.8 x 92.7 mm, 29 parts (0 on the bottom side), 35 nets.

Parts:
C1: 10µF; CP_Radial_D4.0mm_P2.00mm
H1, H2, H3, H4: MountingHole; MountingHole_3.2mm_M3
J1: to LiPo-battery; JST_PH_B2B-PH-K_1x02_P2.00mm_Vertical
J2: to Lolin; JST_PH_B2B-PH-K_1x02_P2.00mm_Vertical
J3: to_Headphone; IDC-Header_2x03_P2.54mm_Vertical
J4: MAX98357a; PinHeader_1x07_P2.54mm_Vertical
J5: Neopixel; JST_PH_B3B-PH-K_1x03_P2.00mm_Vertical
J6: Rotary Encoder; JST_PH_B5B-PH-K_1x05_P2.00mm_Vertical
J7: RFID (PN5180); JST_PH_B10B-PH-K_1x10_P2.00mm_Vertical
J8: Reset; JST_PH_B2B-PH-K_1x02_P2.00mm_Vertical
J9: Next; JST_PH_B2B-PH-K_1x02_P2.00mm_Vertical
J10: Previous; JST_PH_B2B-PH-K_1x02_P2.00mm_Vertical
J11: PPlay; JST_PH_B2B-PH-K_1x02_P2.00mm_Vertical
J12: SD (MMC); PinHeader_1x06_P2.54mm_Vertical
J13: Serial; PinHeader_1x03_P2.54mm_Vertical
JP1: Jumper_NC_Dual; PinHeader_1x03_P2.54mm_Vertical
Q1: IRL3103; TO-220-3_Vertical
Q2: NDP6020P; TO-220-3_Vertical
R1: rdiv1; R_Axial_DIN0204_L3.6mm_D1.6mm_P7.62mm_Horizontal
R2: rdiv2; R_Axial_DIN0204_L3.6mm_D1.6mm_P7.62mm_Horizontal
R3, R6: 100k; R_Axial_DIN0204_L3.6mm_D1.6mm_P7.62mm_Horizontal
R4: 1k; R_Axial_DIN0204_L3.6mm_D1.6mm_P7.62mm_Horizontal
R5, R7: 10k; R_Axial_DIN0204_L3.6mm_D1.6mm_P7.62mm_Horizontal
U1: Lolin32

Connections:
+3V3: J6.2, JP1.3, Q2.3, R6.2, U1.1, U1.20
BUT_NEXT: J9.1, U1.32
BUT_PPLAY: J11.1, U1.28
BUT_PREV: J10.1, R7.1, U1.3
EN: J8.2, U1.2
GND: J3.4, J4.2, J5.3, J6.1, J7.10, J8.1, J9.2, J10.2, J11.2, J12.1, J13.1, Q1.3, R5.1, U1.16, U1.34
HEADPHONE: J3.6, J4.3, U1.14
I2S_BCLK: J3.3, J4.6, U1.11
I2S_DOUT: J3.1, J4.5, U1.9
I2S_LRC: J3.5, J4.7, U1.10
MMC_MISO: J12.2, U1.35
MMC_MOSI: J12.4, U1.36
MMC_SCK: J12.3, U1.12
NEOPIXEL: J5.2, U1.13
unnamed: C1.1, J1.1, J2.1, R1.2
unnamed: C1.2, J1.2, J2.2, R2.2
unnamed: J4.4, R3.1
unnamed: J7.1, J7.2, JP1.2
unnamed: Q1.1, R4.1, R5.2
unnamed: Q1.2, Q2.1, R6.1
unnamed: R4.2, U1.30
RFID_BUSY: J7.8, U1.31
RFID_CS: J7.4, U1.22
RFID_IRQ: J7.9, U1.4
RFID_MISO: J7.6, U1.25
RFID_MOSI: J7.5, U1.26
RFID_RST: J7.3, U1.21
RFID_SCK: J7.7, U1.27
ROTENC_BUT: J6.3, U1.5
ROTENC_CLK: J6.4, U1.7
ROTENC_DT: J6.5, U1.8
RX: J13.3, U1.19
SW_POWER3.3: J3.2, J4.1, J5.1, J12.6, JP1.1, Q2.2, R3.2, R7.2
TX: J13.2, U1.18
VBAT: R1.1, R2.1, U1.6

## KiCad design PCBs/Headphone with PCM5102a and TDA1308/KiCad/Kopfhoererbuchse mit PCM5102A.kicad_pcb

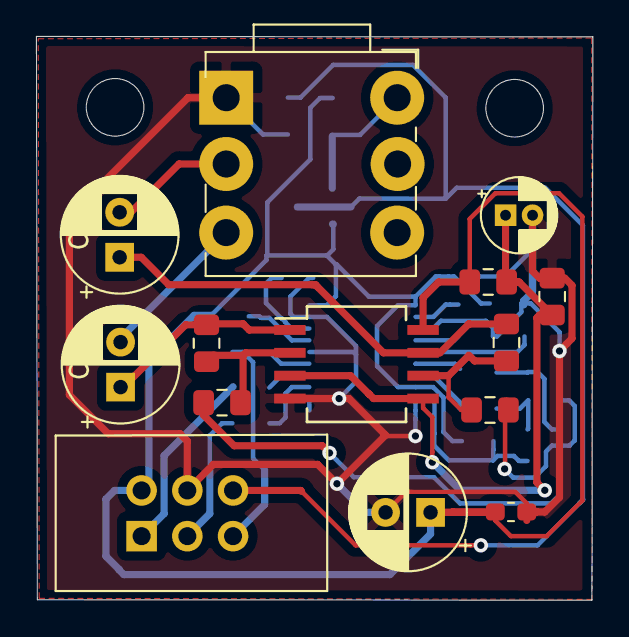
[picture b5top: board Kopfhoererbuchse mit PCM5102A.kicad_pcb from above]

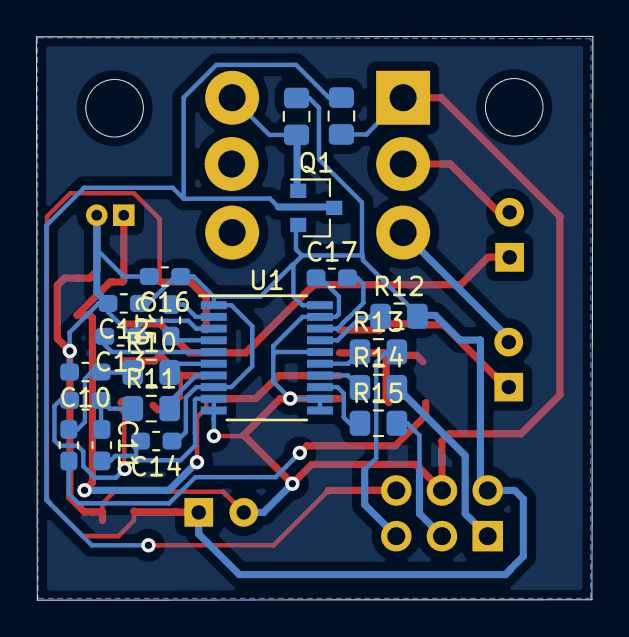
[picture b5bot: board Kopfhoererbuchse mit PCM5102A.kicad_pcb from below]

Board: 2 copper layers, 30.9 x 31.3 mm, 36 parts (20 on the bottom side), 28 nets.

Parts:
C1, C8, C9: 100µ; CP_Radial_D6.3mm_P2.50mm
C2, C12, C14, C16, C17: 100n; C_0603_1608Metric_Pad1.05x0.95mm_HandSolder
C3, C4: 1µ; C_0603_1608Metric_Pad1.05x0.95mm_HandSolder
C5: 22µ; CP_Radial_D4.0mm_P1.50mm
C10, C11: 2,2n; C_0603_1608Metric_Pad1.05x0.95mm_HandSolder
C13, C15: 2,2µ; C_0603_1608Metric_Pad1.05x0.95mm_HandSolder
H1, H2: MountingHole; MountingHole_3.2mm_M3
J1: Conn_02x03_Odd_Even; PinHeader_2x03_P2.54mm_Vertical_large
J2: AudioJack3_Dual_Switch; Jack_3.5mm_Cliff_Horizontal
Q1: IRLML6401; SOT-23
R2, R3, R5, R12: 10k; R_0805_2012Metric_Pad1.15x1.40mm_HandSolder
R4: 100k; R_0805_2012Metric_Pad1.15x1.40mm_HandSolder
R6, R7, R8, R9: 3,9k; R_0805_2012Metric_Pad1.15x1.40mm_HandSolder
R10, R11, R13, R14, R15: 470; R_0805_2012Metric_Pad1.15x1.40mm_HandSolder
U1: PCM5102A; TSSOP-20_4.4x6.5mm_P0.65mm
U2: TDA1308; SO-8_5.3x6.2mm_P1.27mm

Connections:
3,3V: C1.1, C2.1, C12.1, C14.1, C16.1, J1.2, Q1.2, R3.1, R4.2, R12.2, U1.1, U1.8, U1.20, U2.8
BCK: J1.3, R15.2
DIN: J1.1, R14.2
GND: C1.2, C2.2, C5.2, C10.2, C11.2, C12.2, C13.1, C14.2, C16.2, C17.1, J1.4, J2.1, R2.1, R5.2, U1.3, U1.9, U1.10, U1.11, U1.12, U1.16, U1.19, U2.4
LCK: J1.5, R13.2
unnamed: C3.2, R6.1
unnamed: C4.2, R7.1
unnamed: C5.1, R3.2, R5.1, U2.3, U2.5
unnamed: C8.1, R8.2, U2.1
unnamed: C8.2, J2.5
unnamed: C9.1, R9.2, U2.7
unnamed: C9.2, J2.3
unnamed: C13.2, U1.5
unnamed: C15.1, U1.4
unnamed: C15.2, U1.2
unnamed: C17.2, U1.18
unnamed: J1.6, Q1.3, R2.2
unnamed: J2.2, Q1.1, R4.1
unnamed: R6.2, R8.1, U2.2
unnamed: R7.2, R9.1, U2.6
unnamed: R10.2, U1.6
unnamed: R11.2, U1.7
unnamed: R12.1, U1.17
unnamed: R13.1, U1.15
unnamed: R14.1, U1.14
unnamed: R15.1, U1.13
OUTL: C3.1, C10.1, R10.1
OUTR: C4.1, C11.1, R11.1

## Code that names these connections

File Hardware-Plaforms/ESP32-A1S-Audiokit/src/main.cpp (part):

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
// DAC (internal)
#define I2S_DSIN                        25          // internal
#define I2S_BCLK                        27          // internal
#define I2S_LRC                         26          // internal
#define I2S_MCLK                         0          // internal
#define I2S_DOUT                        35          // internal

// I2C GPIOs
#define IIC_CLK                         32          // internal
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// Neopixel-configuration
#ifdef NEOPIXEL_ENABLE
    #define NUM_LEDS                    24          // number of LEDs
    #define CHIPSET                     WS2812B     // type of Neopixel
    #define COLOR_ORDER                 GRB
#endif

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// Configuration of initial values (for the first start) goes here....
// There's no need to change them here as they can be configured via webinterface
// Neopixel
uint8_t initialLedBrightness = 16;                      // Initial brightness of Neopixel
uint8_t ledBrightness = initialLedBrightness;
uint8_t nightLedBrightness = 2;                         // Brightness of Neopixel in nightmode

// MQTT
bool enableMqtt = true;
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        delay(1000);
    }

    audio.setPinout(I2S_BCLK, I2S_LRC, I2S_DSIN);
    audio.setVolume(initVolume);

    pinMode(GPIO_PA_EN, OUTPUT);
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    static uint8_t trackCommand = 0;

    for (;;) {
        // GPIO is 0 if headphone is plugged in. So turn of speaker if so and vice versa.
        currentHeadphoneState = digitalRead(HEADPHONE_PLUGGED_IN);
        if (((lastHeadphoneState != currentHeadphoneState) && (millis() - lastHeadphoneStateTimestamp >= 1000)) || !lastHeadphoneStateTimestamp) {
            if (!currentHeadphoneState) {
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// Instructs RFID-scanner to scan for new RFID-tags
void rfidScanner(void *parameter) {
    //static MFRC522 mfrc522(MFRC522_CS_PIN, MFRC522_RST_PIN);
    //static MFRC522 mfrc522(RFID_CS, RST_PIN);
    //SPI.begin();
    mfrc522.PCD_Init();
    mfrc522.PCD_DumpVersionToSerial();  // Show details of PCD - MFRC522 Card Reader detail
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
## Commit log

2021-02-13 add symbol and footprint for Lolin32-lite source: https://gitlab.com/kicad/libraries/kicad-footprints/-/merge_requests/2554 https://gitlab.com/kicad/libraries/kicad-symbols/-/merge_requests/3148
2021-02-13 add Kicad-Files from before cc6df6d
2021-02-13 KiCad-Files umbenennen: Kopfhoererplatine
2021-02-13 KiCad-Files umbenennen: ESP32_Breakout_Carrier
2021-02-13 Kicad-Files entpacken
2021-02-13 KiCad-Files umbenennen: Lolin32
2021-02-13 KiCad-Files umbenennen: Lolin D32
2021-02-13 KiCad-Files umbenennen: Lolin32 SD_MMC PN5180
2021-02-13 move Lolin32 Lite KiCad libraries - add license notice
2021-02-13 move KiCad files to old location
2021-02-13 add KiCad-Files from SnapEDA & add license notice
2021-02-13 re-generate gerber files for all PCBs
2021-02-13 re-generate gerber files for ESP32_Breakout_Carrier
2021-02-14 use snapEDA footprint and create 3d-model for ESP32_Breakout_Carrier
2021-02-14 rename Toniuno -> ESPuino
2021-02-14 rename Tonuino -> ESPuino: create new Schematics
2021-03-02 copy board json files from ~/.platformio/…
2021-03-02 add USB PIDs/VIDs to board json files
2021-03-02 remove hardcoded upload/monitor ports from platformio.ini
2021-03-02 change Documentation for autodetection of ports

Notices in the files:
PCBs/ESP32_Breakout_Carrier/KiCad/ESPuino.kicad_pcb:
CC-BY-SA mariolukas.de
